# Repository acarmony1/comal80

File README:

In December of 2020 I was asked by KEN SIMMONS to create a comal-80 cartridge, for the Commodore 64, from an old COMAL TODAY magazine schematic. The COMAL80 cartridge uses unique 'bankswithcing' to switch up to 96KB of ROM.

This project is a result of that task. 

The board is a simple 2 layer design, with (3) 27C256 EPROMS, and (3) logic devices (74LS86, 74LS161, 74LS139), others may be substitued but are not known at this time.

The gerber files for creating a PCB are located in the gerbers directory. The bin files for U1 and U2 are located in the bin folder. U3 is left empty, and is used for personal spece (if needed) for user applications. There is a 'superchip' that existed to allow for expansion of the COMAL 80 system, however I cannot locate this bin currently.

1-18-2021	GutHub creation and release of V1. Design is known working and completed. No known issues or releases planned.

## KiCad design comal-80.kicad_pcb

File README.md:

# comal80
COMAL 80 for C64
https://carmony.xyz/10-commodore/commodore-64-projects/2-comal-80-for-the-c64.html

or visit https://carmony.xyz for other infomation.

In December of 2020 I was asked by KEN SIMMONS to create a comal-80 cartridge, for the Commodore 64, from an old COMAL TODAY magazine schematic. The COMAL80 cartridge uses unique 'bankswithcing' to switch up to 96KB of ROM.

This project is a result of that task. 

The board is a simple 2 layer design, with (3) 27C256 EPROMS, and (3) logic devices (74LS86, 74LS161, 74LS139), others may be substitued but are not known at this time.

The gerber files for creating a PCB are located in the gerbers directory. The bin files for U1 and U2 are located in the bin folder. U3 is left empty, and is used for personal space (if needed) for user applications, called packages. There is a 'superchip' that existed to allow for expansion of the COMAL 80 system, however I cannot locate this bin currently.

1-18-2021	GutHub creation and release of V1. Design is known working and completed. No known issues or releases planned. 

1-19-2021 C64/C128 folders added. C128 Comal Cartridge schematic added.

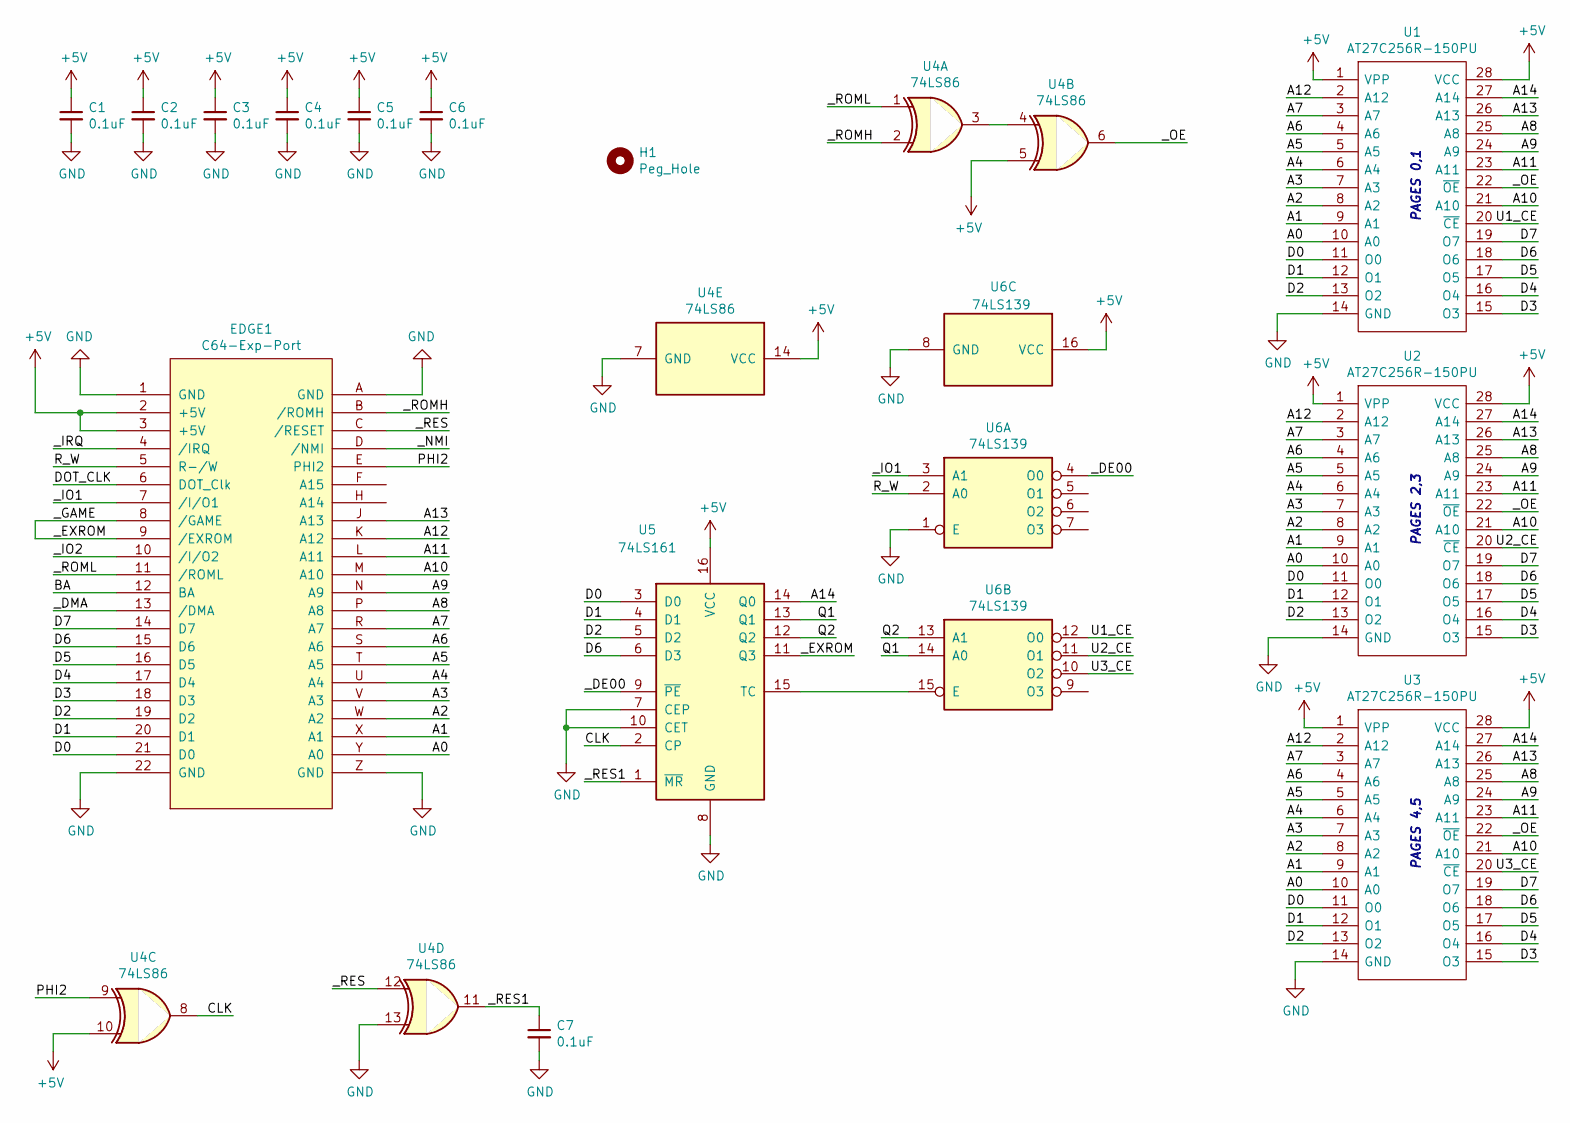
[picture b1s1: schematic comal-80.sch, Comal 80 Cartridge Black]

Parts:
C1, C2, C3, C4, C5, C6, C7: 0.1uF; C_Disc_D3.0mm_W1.6mm_P2.50mm
EDGE1: C64-Exp-Port; C64-Cart
H1: Peg_Hole; MountingHole_5mm_Pad
U1, U2, U3: AT27C256R-150PU; DIP-28_W15.24mm_Socket; Manufacturer_Part_Number AT27C256R-70PU; Mouser Part Number 556-AT27C256R70PU
U4: 74LS86; DIP-14_W7.62mm_Socket
U5: 74LS161; DIP-16_W7.62mm_Socket
U6: 74LS139; DIP-16_W7.62mm_Socket

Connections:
+5V: C1.1, C2.1, C3.1, C4.1, C5.1, C6.1, EDGE1.2 (+5V), EDGE1.3 (+5V), U1.1 (VPP), U1.28 (VCC), U2.1 (VPP), U2.28 (VCC), U3.1 (VPP), U3.28 (VCC), U4.5, U4.10, U4.14 (VCC), U5.16 (VCC), U6.16 (VCC)
/A0: EDGE1.Y (A0), U1.10 (A0), U2.10 (A0), U3.10 (A0)
/A1: EDGE1.X (A1), U1.9 (A1), U2.9 (A1), U3.9 (A1)
/A2: EDGE1.W (A2), U1.8 (A2), U2.8 (A2), U3.8 (A2)
/A3: EDGE1.V (A3), U1.7 (A3), U2.7 (A3), U3.7 (A3)
/A4: EDGE1.U (A4), U1.6 (A4), U2.6 (A4), U3.6 (A4)
/A5: EDGE1.T (A5), U1.5 (A5), U2.5 (A5), U3.5 (A5)
/A6: EDGE1.S (A6), U1.4 (A6), U2.4 (A6), U3.4 (A6)
/A7: EDGE1.R (A7), U1.3 (A7), U2.3 (A7), U3.3 (A7)
/A8: EDGE1.P (A8), U1.25 (A8), U2.25 (A8), U3.25 (A8)
/A9: EDGE1.N (A9), U1.24 (A9), U2.24 (A9), U3.24 (A9)
/A10: EDGE1.M (A10), U1.21 (A10), U2.21 (A10), U3.21 (A10)
/A11: EDGE1.L (A11), U1.23 (A11), U2.23 (A11), U3.23 (A11)
/A12: EDGE1.K (A12), U1.2 (A12), U2.2 (A12), U3.2 (A12)
/A13: EDGE1.J (A13), U1.26 (A13), U2.26 (A13), U3.26 (A13)
/A14: U1.27 (A14), U2.27 (A14), U3.27 (A14), U5.14 (Q0)
/BA: EDGE1.12 (BA)
/CLK: U4.8, U5.2 (CP)
/D0: EDGE1.21 (D0), U1.11 (O0), U2.11 (O0), U3.11 (O0), U5.3 (D0)
/D1: EDGE1.20 (D1), U1.12 (O1), U2.12 (O1), U3.12 (O1), U5.4 (D1)
/D2: EDGE1.19 (D2), U1.13 (O2), U2.13 (O2), U3.13 (O2), U5.5 (D2)
/D3: EDGE1.18 (D3), U1.15 (O3), U2.15 (O3), U3.15 (O3)
/D4: EDGE1.17 (D4), U1.16 (O4), U2.16 (O4), U3.16 (O4)
/D5: EDGE1.16 (D5), U1.17 (O5), U2.17 (O5), U3.17 (O5)
/D6: EDGE1.15 (D6), U1.18 (O6), U2.18 (O6), U3.18 (O6), U5.6 (D3)
/D7: EDGE1.14 (D7), U1.19 (O7), U2.19 (O7), U3.19 (O7)
/DOT_CLK: EDGE1.6 (DOT_Clk)
/PHI2: EDGE1.E (PHI2), U4.9
/Q1: U5.13 (Q1), U6.14 (A0)
/Q2: U5.12 (Q2), U6.13 (A1)
/R_W: EDGE1.5 (R-/W), U6.2 (A0)
/U1_CE: U1.20 (~CE), U6.12 (O0)
/U2_CE: U2.20 (~CE), U6.11 (O1)
/U3_CE: U3.20 (~CE), U6.10 (O2)
/_DE00: U5.9 (~PE), U6.4 (O0)
/_DMA: EDGE1.13 (/DMA)
/_EXROM: EDGE1.8 (/GAME), EDGE1.9 (/EXROM), U5.11 (Q3)
/_IO1: EDGE1.7 (/I/O1), U6.3 (A1)
/_IO2: EDGE1.10 (/I/O2)
/_IRQ: EDGE1.4 (/IRQ)
/_NMI: EDGE1.D (/NMI)
/_OE: U1.22 (~OE), U2.22 (~OE), U3.22 (~OE), U4.6
/_RES: EDGE1.C (/RESET), U4.12
/_RES1: C7.1, U4.11, U5.1 (~MR)
/_ROMH: EDGE1.B (/ROMH), U4.2
/_ROML: EDGE1.11 (/ROML), U4.1
GND: C1.2, C2.2, C3.2, C4.2, C5.2, C6.2, C7.2, EDGE1.1 (GND), EDGE1.22 (GND), EDGE1.A (GND), EDGE1.Z (GND), U1.14 (GND), U2.14 (GND), U3.14 (GND), U4.7 (GND), U4.13, U5.7 (CEP), U5.8 (GND), U5.10 (CET), U6.1 (E), U6.8 (GND)
unnamed: U4.3, U4.4
unnamed: U5.15 (TC), U6.15 (E)

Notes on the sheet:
PAGES 4,5
PAGES 2,3
PAGES 0,1

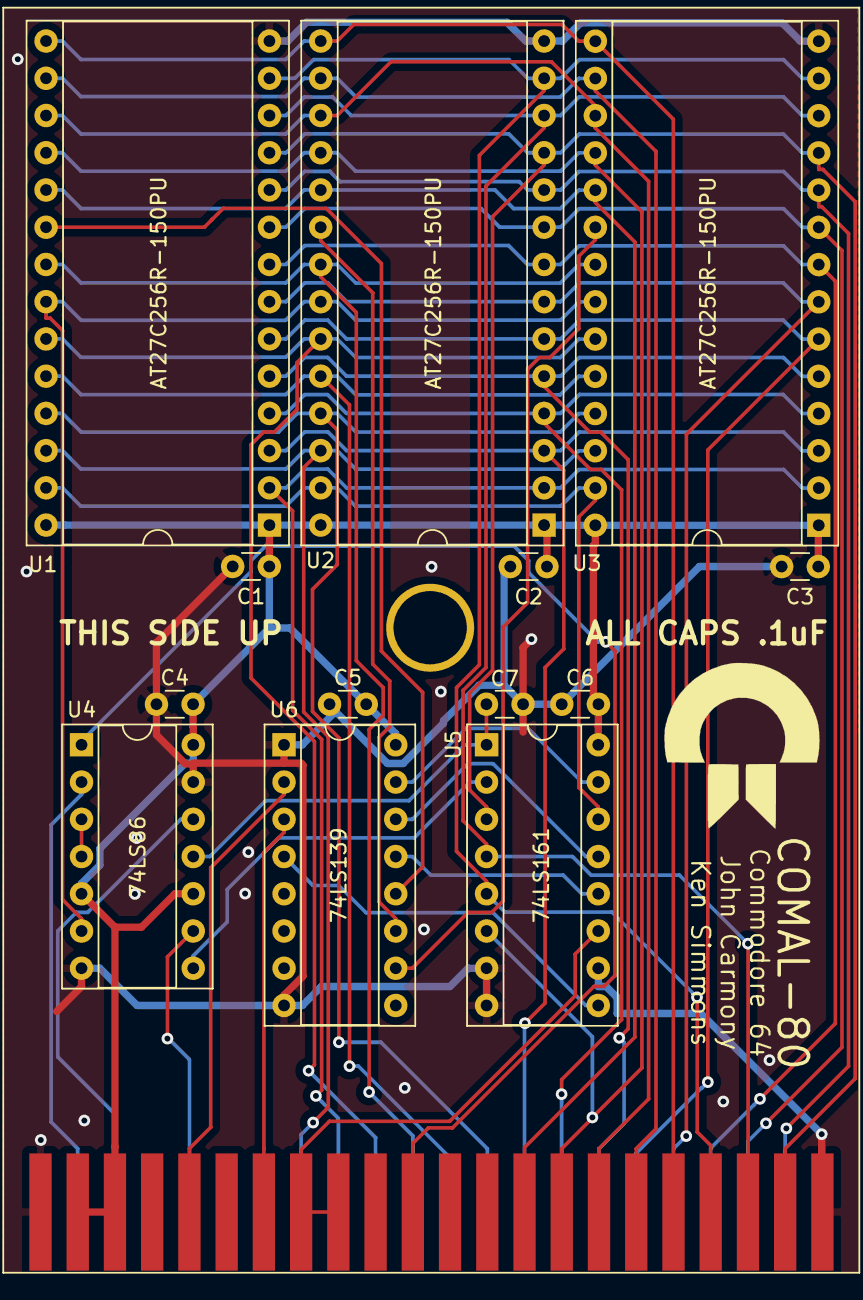
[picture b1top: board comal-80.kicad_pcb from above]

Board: 2 copper layers, 15 parts (0 on the bottom side), 43 nets.

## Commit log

2021-01-18 First update
2021-01-18 Schematic Housekeeping
    Adjustments made to schematic, updated PDF
2021-01-18 Moved bin files
    Moved bin files to their proper place
2021-01-18 Changed README.MD
2021-01-18 Added 3D pic
2021-01-18 Delete comal-80 - Copy.kicad_pcb
    removed some files.
2021-01-19 Added C128 schematic
    Created C64 and C128 folders and added C128 comal cart schematic
2021-01-19 Added readme.md to C64/C128
2021-01-20 Added 3 C128 Comal-80 bun files
    Added U1, U2, U3 ROM bin files.
2021-01-20 Update README.md
    Updated README.md
2021-01-22 Updated C128 README.md
    C128 schematic is un-useable

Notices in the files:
comal-80.sch:
Commodore Denmark (PUBLIC DOMAIN)
